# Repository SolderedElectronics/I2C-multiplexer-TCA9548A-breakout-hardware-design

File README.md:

# I2C multiplexer TCA9548A breakout Hardware Design

## About the Product

|  |
| :----------------------------------------------------------: |
| [Buy I2C multiplexer TCA9548A breakout](https://www.solde.red/333077) |

Have you ever found yourself wanting to connect more than one I2C device to a single controller and couldn’t because they have identical I2C addresses? There you have it, I2C multiplexer (I2C MUX) allows you to use up to 8 devices with the same address on the same bus! If we mention that TCA9548A, the IC on which this breakout is based, has three adjustable pins for the I2C address, which means a total of 8 possible addresses. We can reach 64 devices with the same address on the same bus. For example, it is possible to connect 64 BME680 sensors that are read by only one microcontroller.

This adapter is particularly practical because it enables multiplexing of qwiic devices. 

---

## Repository Contents

This repository contains all design files for I2C multiplexer TCA9548A breakout, organized as follows:

- **`CAD` folder**: Contains KiCAD design files, including:
  - Schematics
  - PCB layout
  - Panel PCB layout
  - Source 3D files in Fusion360, if any
  - All files are sorted by version with a detailed change log.
- **`OUTPUTS` folder**: Includes all production-ready files, such as:
  - Bill of Materials (BOM) and interactive BOM (iBOM)
  - PDF versions of schematics
  - 3D `.step` file of the board
  - 3D-printable models
  - Gerber files for PCB manufacturing
  - Image of the pinout of the board
  - Product image
  - Compliance, legal and generic sales documents

Refer to the `Change Log` in the CAD folder for details about updates between versions.

---

## Learn More About the Product

Beyond the repository, explore the following resources:

### Soldered Verify

The **Soldered Verify** system ensures every board you purchase from Soldered is fully functional. It also provides access to exclusive test data for your product. To get started, find the unique Soldered Verify ID on your product's packaging and enter the ID on the [Soldered Verify page](https://soldered.com/verify/) to access test results and additional product details.

### Soldered Community

Soldered Community is your go-to place for technical support. Our engineers track and answer all questions posted there, and it’s a great space for the maker community. Get answers to your questions and solutions for your challenges at [Soldered Community](https://soldered.com/community).

### solde.red

solde.red is an ultimate URL shortener and information hub. Access it by typing solde.red/ followed by your product SKU, e.g., [solde.red/333000](https://solde.red/333000), to find getting-started guides, datasheets, open-source hardware and software files, certifications, images, pinouts, and more. Read more about the shortener [here](https://solde.red/info/).

---

## Contributing

Contributions are welcome! Here’s how you can get involved:

- Submit pull requests to enhance the design or fix issues.
- Report bugs or problems by opening an issue.

We encourage community collaboration to make this product even better.

---

## About Soldered

[Soldered for Makers](https://soldered.com) specializes in designing and manufacturing electronic products tailored for enthusiasts, ranging from hobbyists to professionals. Our portfolio includes electronic boards, sensors, and actuators that are widely utilized in fields such as microelectronics, mechatronics, robotics, programming, and IoT. Every product we offer is designed in-house and built upon open-source hardware and software platforms. Proudly certified and manufactured within the European Union, our catalog likely includes the product you need for your project.

We complement these products with comprehensive tutorials and manuals, product descriptions, schematics, programming codes, and project examples. Our round-the-clock [customer and technical support](https://soldered.com/community) is available for all our products, irrespective of the sales channel. Soldered’s success and services reflect our maker community’s unwavering [trust](https://www.trustpilot.com/review/soldered.com), for which we are deeply grateful. Join our community and create using Soldered products.

---

## License

All Soldered open-source hardware (OSH) is under The TAPR Open Hardware License. Read more in the LICENSE file located in this repository.

**Disclaimer:**

No warranty - all designs in this repository are distributed in the hope that they will be useful, but without any warranty. They are provided "AS IS", therefore without warranty of any kind, either expressed or implied. The entire quality and performance of what you do with the contents of this repository are your responsibility. In no event Soldered Electronics will be liable for your damages, or losses, including any general, special, incidental, or consequential damage arising out of the use or inability to use the contents of this repository. 

---

## Have fun!

Thank you for your support from your fellow makers at Soldered Electronics.

Happy Making!

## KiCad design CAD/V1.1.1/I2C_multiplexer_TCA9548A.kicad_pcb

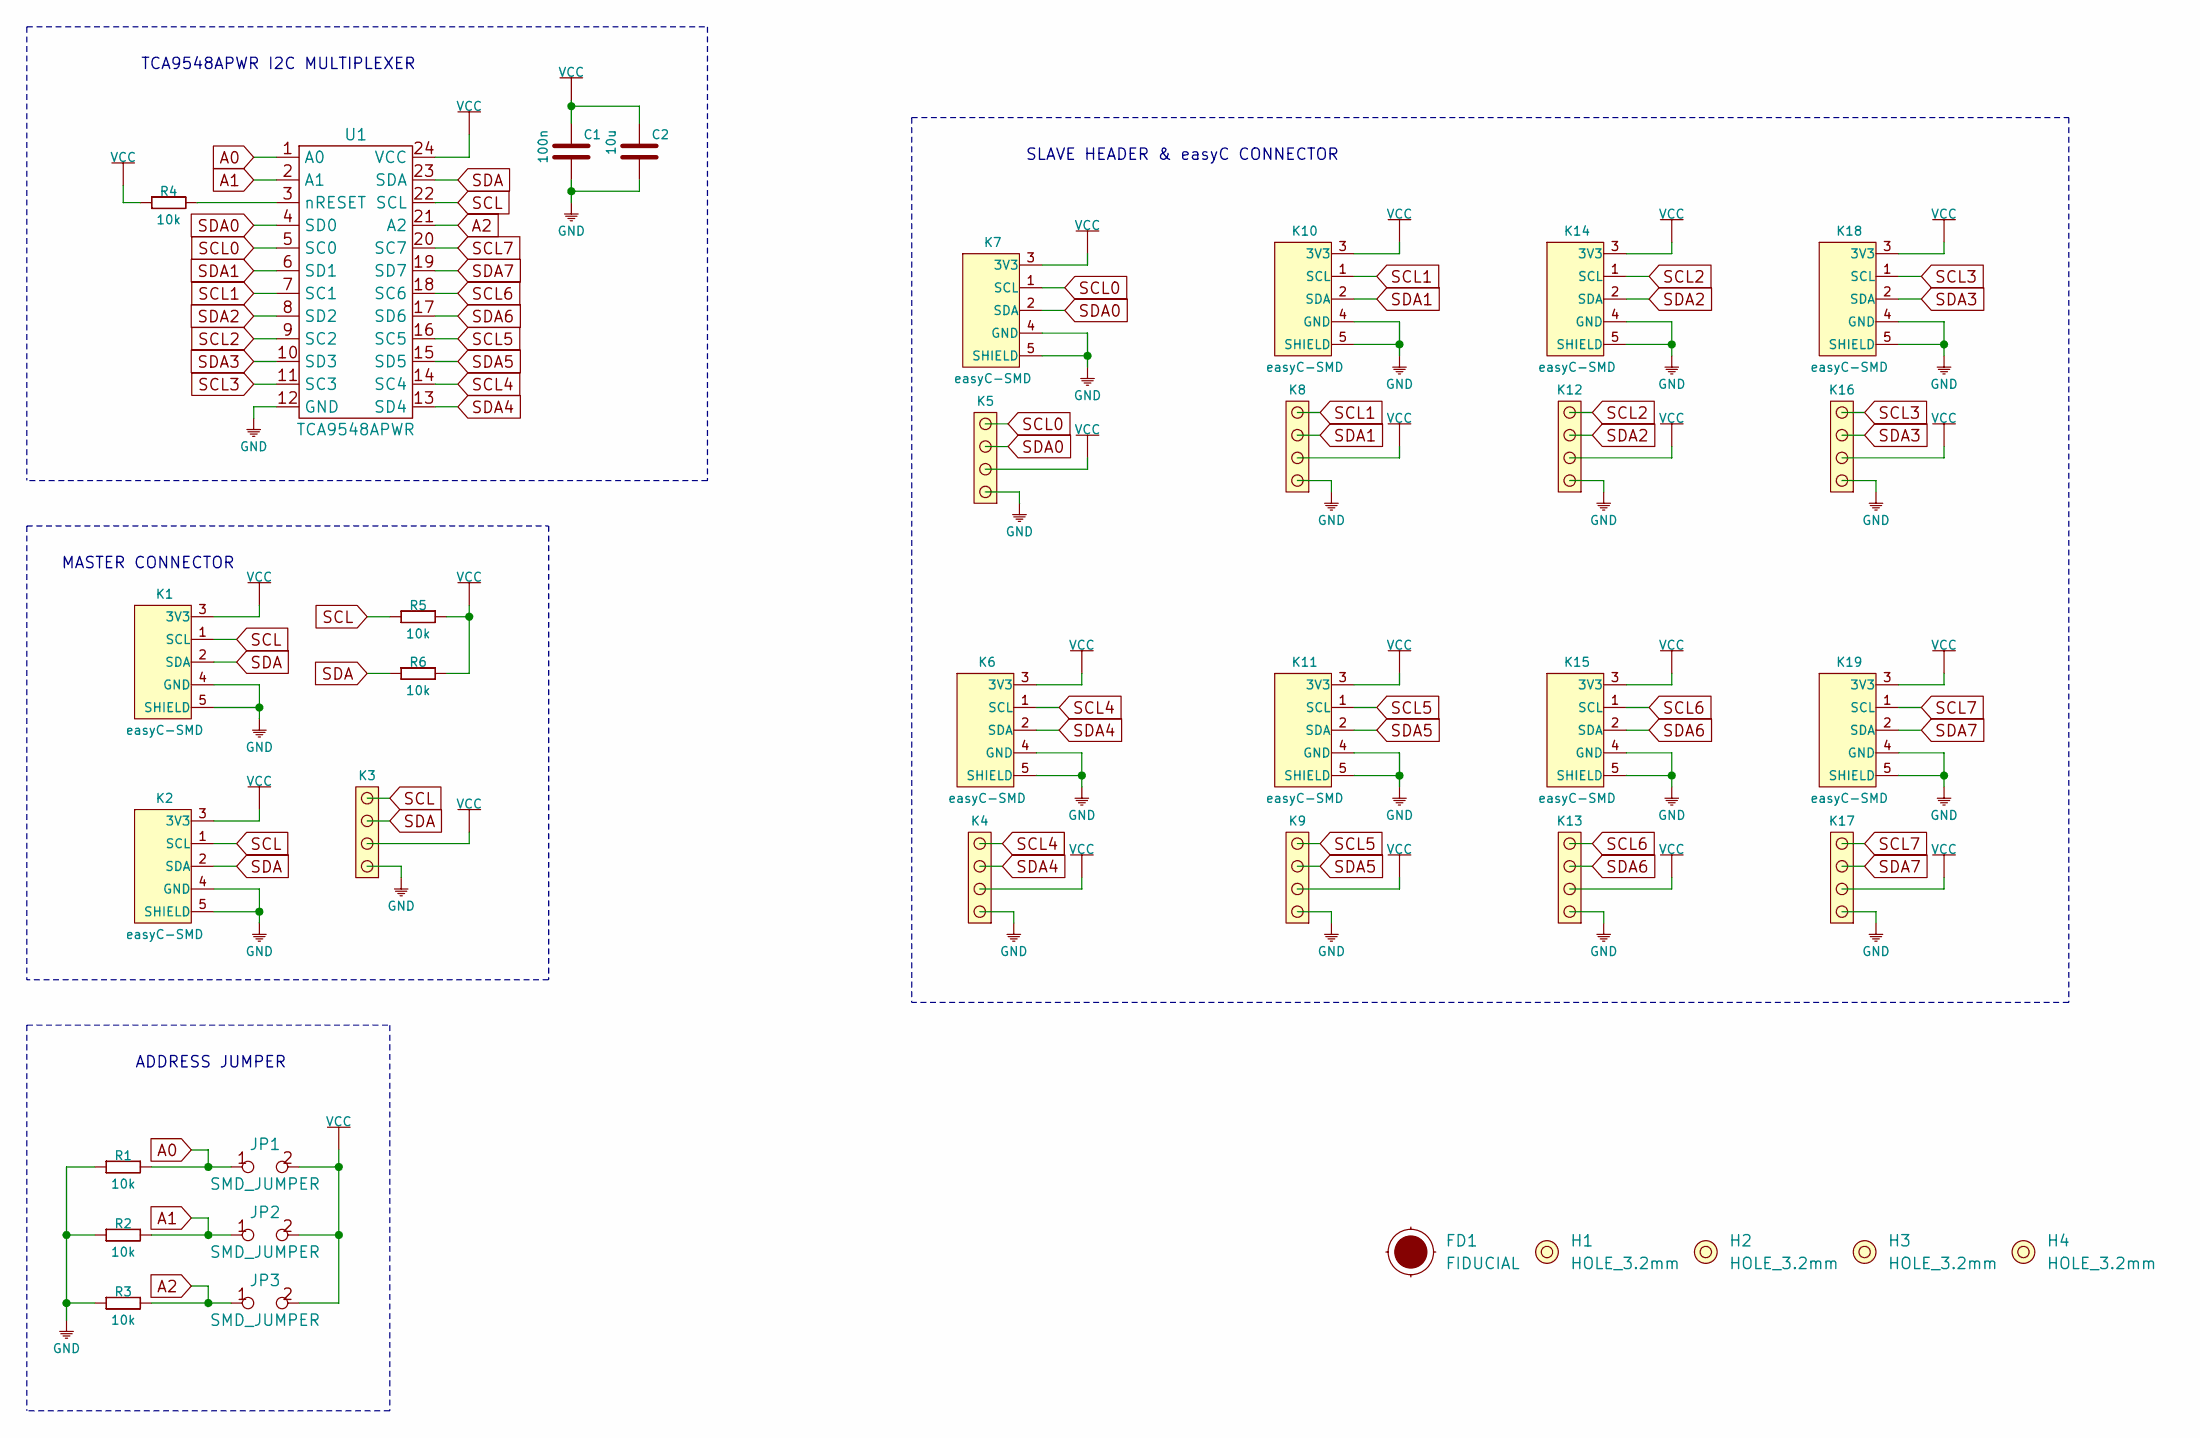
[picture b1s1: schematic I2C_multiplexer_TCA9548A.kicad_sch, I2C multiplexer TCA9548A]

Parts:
C1: 100n; 0603C
C2: 10u; 1206C
FD1: FIDUCIAL; FIDUCIAL_23
H1, H2, H3, H4: HOLE_3.2mm
JP1, JP2, JP3: SMD_JUMPER
K1, K2, K6, K7, K10, K11, K14, K15, K18, K19: easyC-SMD; easyC-connector
K3, K4, K5, K8, K9, K12, K13, K16, K17: HEADER_MALE_4X1
R1, R2, R3, R4, R5, R6: 10k; 0603R
U1: TCA9548APWR; TSSOP-24

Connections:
A0: JP1.1, R1.2, U1.1 (A0)
A1: JP2.1, R2.2, U1.2 (A1)
A2: JP3.1, R3.2, U1.21 (A2)
GND: C1.1, C2.2, K1.4 (GND), K1.5 (SHIELD), K2.4 (GND), K2.5 (SHIELD), K3.1, K4.1, K5.1, K6.4 (GND), K6.5 (SHIELD), K7.4 (GND), K7.5 (SHIELD), K8.1, K9.1, K10.4 (GND), K10.5 (SHIELD), K11.4 (GND), K11.5 (SHIELD), K12.1, K13.1, K14.4 (GND), K14.5 (SHIELD), K15.4 (GND), K15.5 (SHIELD), K16.1, K17.1, K18.4 (GND), K18.5 (SHIELD), K19.4 (GND), K19.5 (SHIELD), R1.1, R2.1, R3.1, U1.12 (GND)
unnamed: R4.2, U1.3 (nRESET)
SCL: K1.1 (SCL), K2.1 (SCL), K3.4, R5.1, U1.22 (SCL)
SCL0: K5.4, K7.1 (SCL), U1.5 (SC0)
SCL1: K8.4, K10.1 (SCL), U1.7 (SC1)
SCL2: K12.4, K14.1 (SCL), U1.9 (SC2)
SCL3: K16.4, K18.1 (SCL), U1.11 (SC3)
SCL4: K4.4, K6.1 (SCL), U1.14 (SC4)
SCL5: K9.4, K11.1 (SCL), U1.16 (SC5)
SCL6: K13.4, K15.1 (SCL), U1.18 (SC6)
SCL7: K17.4, K19.1 (SCL), U1.20 (SC7)
SDA: K1.2 (SDA), K2.2 (SDA), K3.3, R6.1, U1.23 (SDA)
SDA0: K5.3, K7.2 (SDA), U1.4 (SD0)
SDA1: K8.3, K10.2 (SDA), U1.6 (SD1)
SDA2: K12.3, K14.2 (SDA), U1.8 (SD2)
SDA3: K16.3, K18.2 (SDA), U1.10 (SD3)
SDA4: K4.3, K6.2 (SDA), U1.13 (SD4)
SDA5: K9.3, K11.2 (SDA), U1.15 (SD5)
SDA6: K13.3, K15.2 (SDA), U1.17 (SD6)
SDA7: K17.3, K19.2 (SDA), U1.19 (SD7)
VCC: C1.2, C2.1, JP1.2, JP2.2, JP3.2, K1.3 (3V3), K2.3 (3V3), K3.2, K4.2, K5.2, K6.3 (3V3), K7.3 (3V3), K8.2, K9.2, K10.3 (3V3), K11.3 (3V3), K12.2, K13.2, K14.3 (3V3), K15.3 (3V3), K16.2, K17.2, K18.3 (3V3), K19.3 (3V3), R4.1, R5.2, R6.2, U1.24 (VCC)

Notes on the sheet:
SLAVE HEADER & easyC CONNECTOR
TCA9548APWR I2C MULTIPLEXER
ADDRESS JUMPER
MASTER CONNECTOR

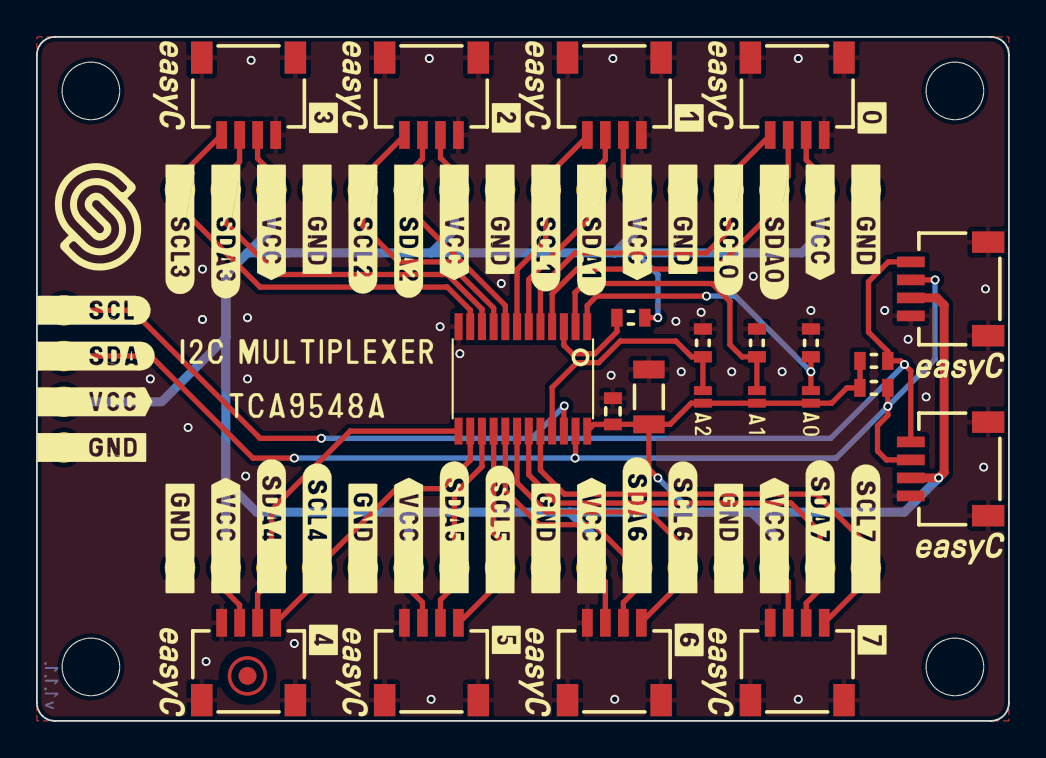
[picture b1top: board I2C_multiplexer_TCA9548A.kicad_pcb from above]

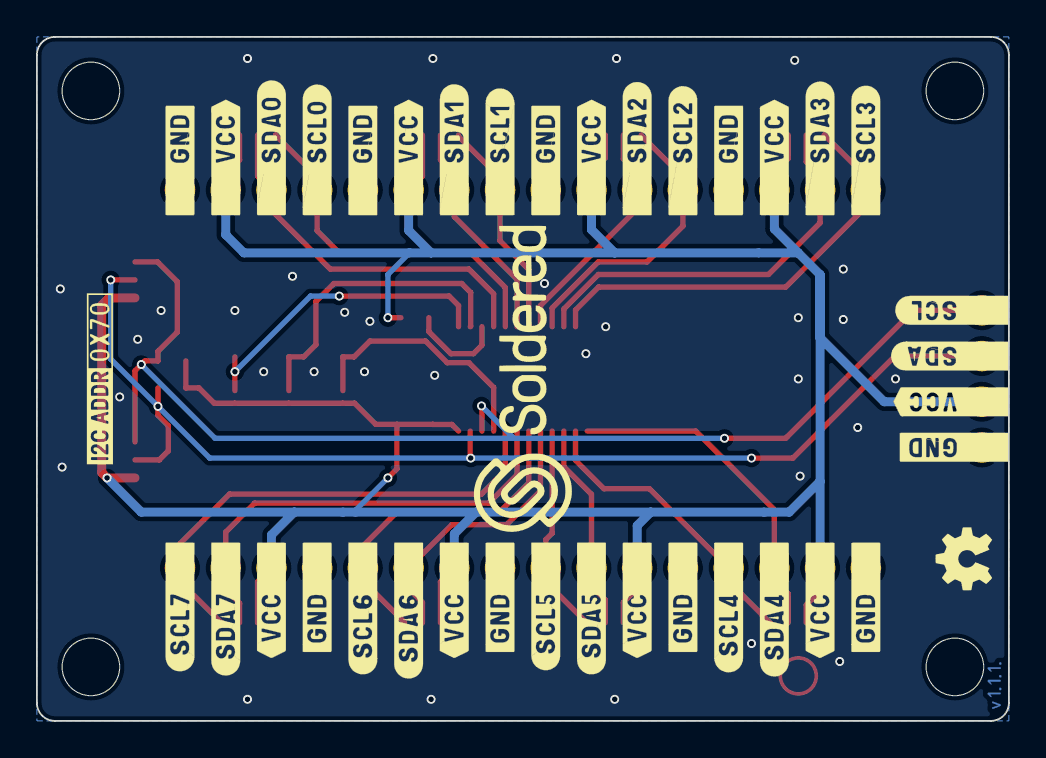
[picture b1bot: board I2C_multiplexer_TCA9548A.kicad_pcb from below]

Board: 2 copper layers, 54.0 x 38.0 mm, 36 parts (9 on the bottom side), 24 nets.

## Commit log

2022-08-06 Updating open source files.
